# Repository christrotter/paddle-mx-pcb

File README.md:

# paddle-mx-pcb
Simple 3-switch pcb for mk20 paddle switches.

I'd wanted to have remote mechanisms activate mx switches for my 'paddle switch' functionality.  It ended up being very complicated and unnecessary, difficult to package up.  It would have been simple to have the location complexity be in printable parts, and the pcb be very simple.  Alas.

Superceded by: https://github.com/christrotter/paddle-dpad-pcb

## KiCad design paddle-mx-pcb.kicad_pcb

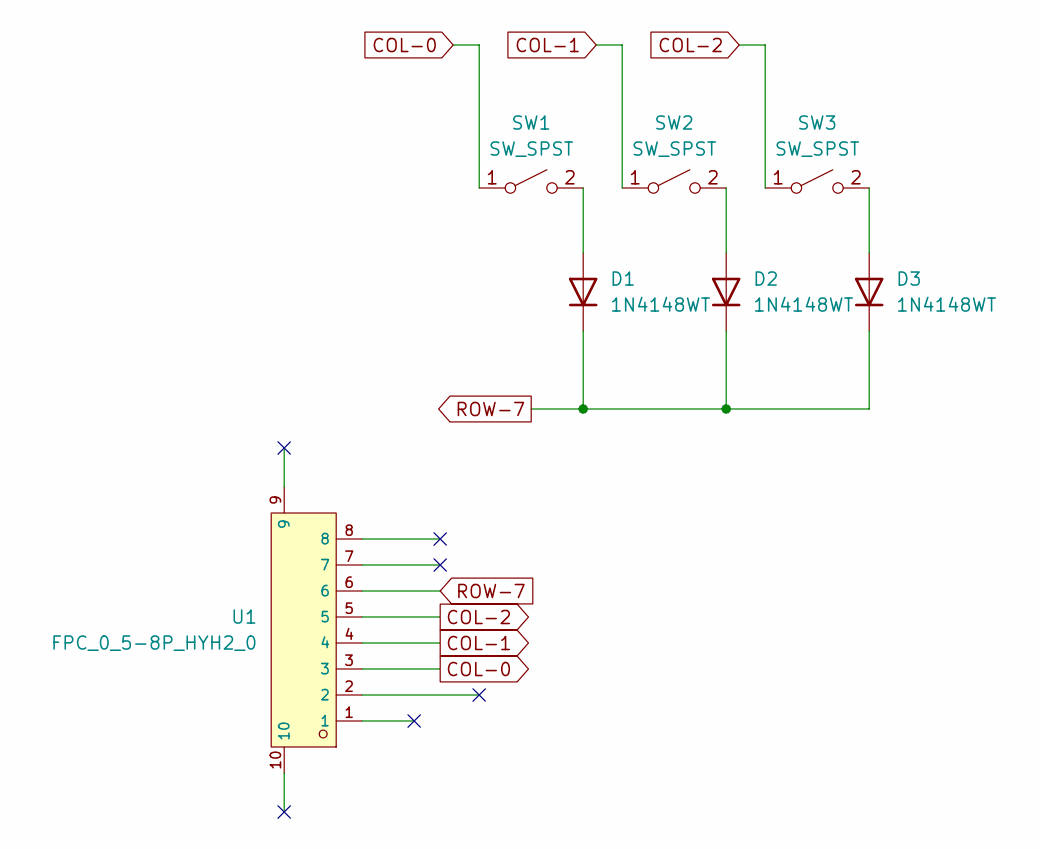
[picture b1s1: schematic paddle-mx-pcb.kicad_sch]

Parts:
D1, D2, D3: 1N4148WT; D_SOD-523
SW1, SW2, SW3: SW_SPST; Kailh_socket_MX
U1: FPC_0_5-8P_HYH2_0; FPC-SMD_8P-P0.50_8.01A0.008200; LCSC C6364658

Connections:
COL-0: SW1.1 (A), U1.3
COL-1: SW2.1 (A), U1.4
COL-2: SW3.1 (A), U1.5
unnamed: D1.2 (A), SW1.2 (B)
unnamed: D2.2 (A), SW2.2 (B)
unnamed: D3.2 (A), SW3.2 (B)
ROW-7: D1.1 (K), D2.1 (K), D3.1 (K), U1.6

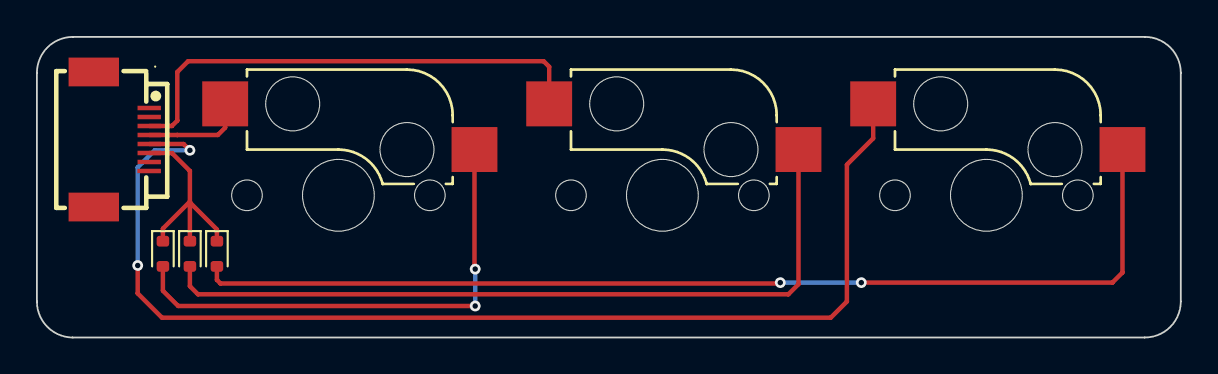
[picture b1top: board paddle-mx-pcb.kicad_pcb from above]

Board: 2 copper layers, 63.6 x 16.7 mm, 7 parts (3 on the bottom side), 7 nets.

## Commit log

2025-07-12 abandoned, but saving my notes
2025-07-12 updating readme
